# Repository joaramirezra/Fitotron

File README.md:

# Recamara de ambiente Controlado para germinar semillas de cannabis(Fitotron) 
### version : 0.2
### Fecha : 01/08/2021

**Antecedentes:** En el marco de la discusión de la propuesta del proyecto de ley sobre  regulación del consumo de cannabis con usos recreativo en Colombia, se han desarrollado debates en variados ámbitos algunos versan alrededor del cultivo,iacto economico, social, cultural  entre otros, por lo anterior se desarrolla un sistema de germinacion de semillas de cannabis, para poder impactar de manera positiva las primeras fases de la planta y con ellos contribuir en fases posteriores de crecimiento y cosecha.

**Descripción:**

### Requerimientos

**Hardware:**

- [ESP 8266](https://www.espressif.com/sites/default/files/documentation/0a-esp8266ex_datasheet_en.pdf)
- [Driver Actuadores](http://www.ti.com/lit/ds/symlink/uln2003a.pdf)
- [Sensor Humedad](https://www.sparkfun.com/datasheets/Sensors/Temperature/DHT22.pdf)
- [Raspberry pi]()

**Software:**

- [kicad 5.1.2](https://kicad-pcb.org/download/)
- [inventor 2019](https://www.autodesk.com/education/free-software/inventor-professional)
- [Arduino 18.1](https://www.arduino.cc/en/main/software)

### Colaboradores:
- [Johan Ramirez](https://github.com/joaramirezra)
- [Julio Cárdenas](https://github.com/julio-cardenas)

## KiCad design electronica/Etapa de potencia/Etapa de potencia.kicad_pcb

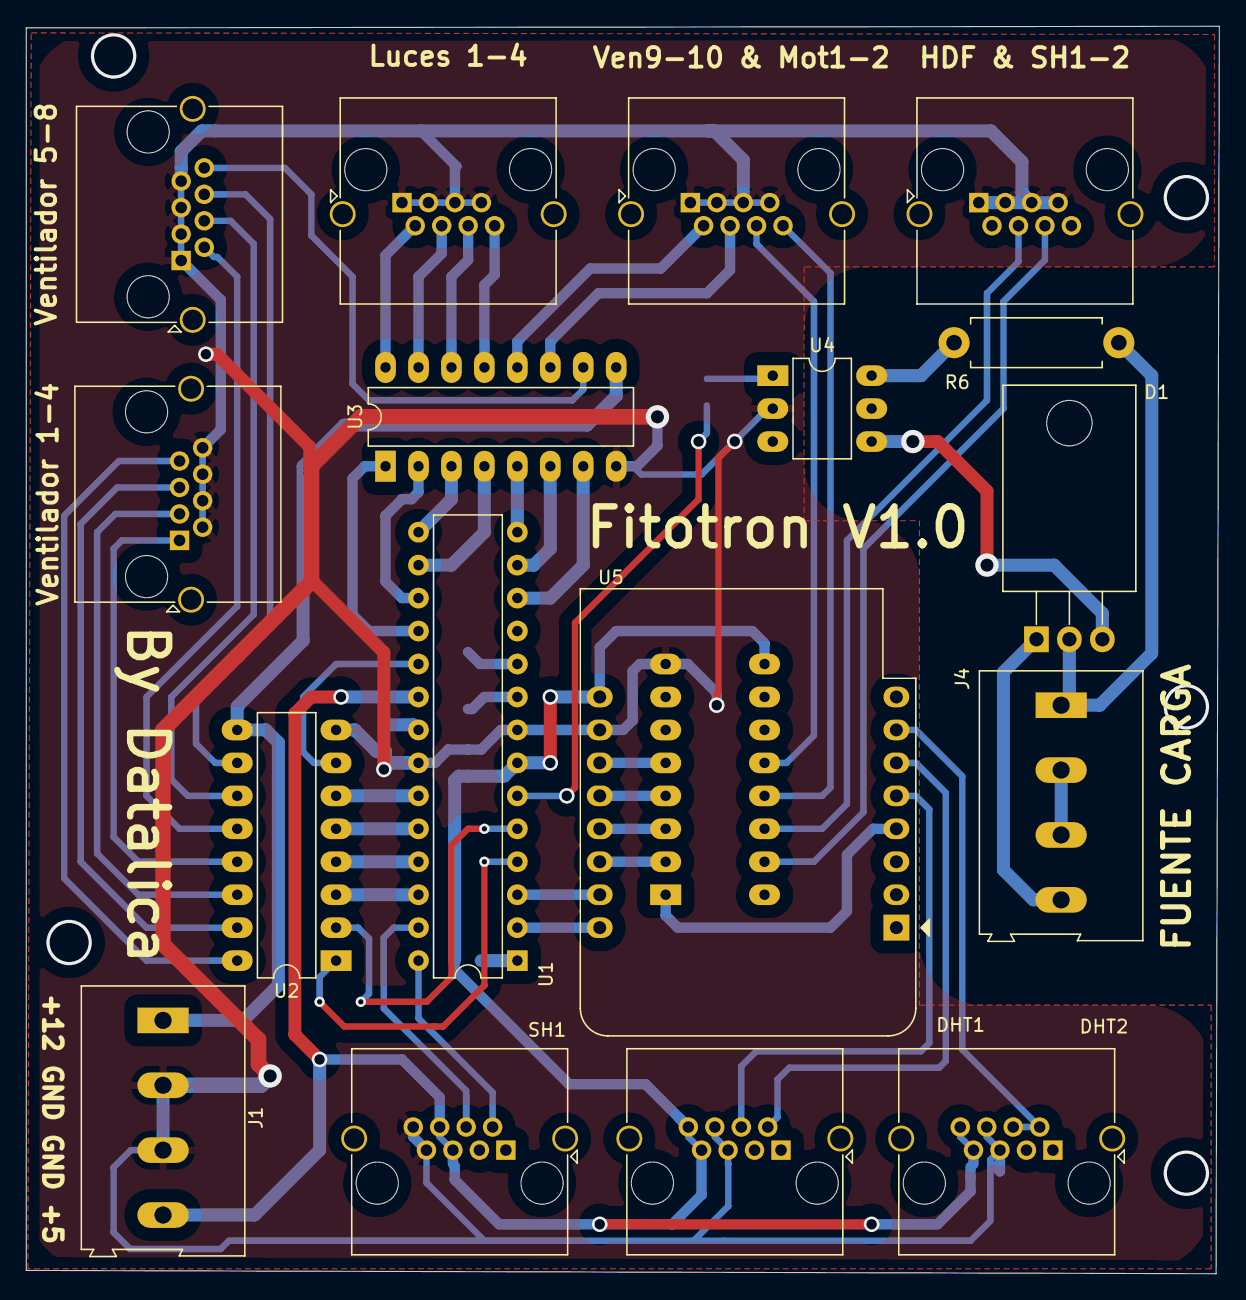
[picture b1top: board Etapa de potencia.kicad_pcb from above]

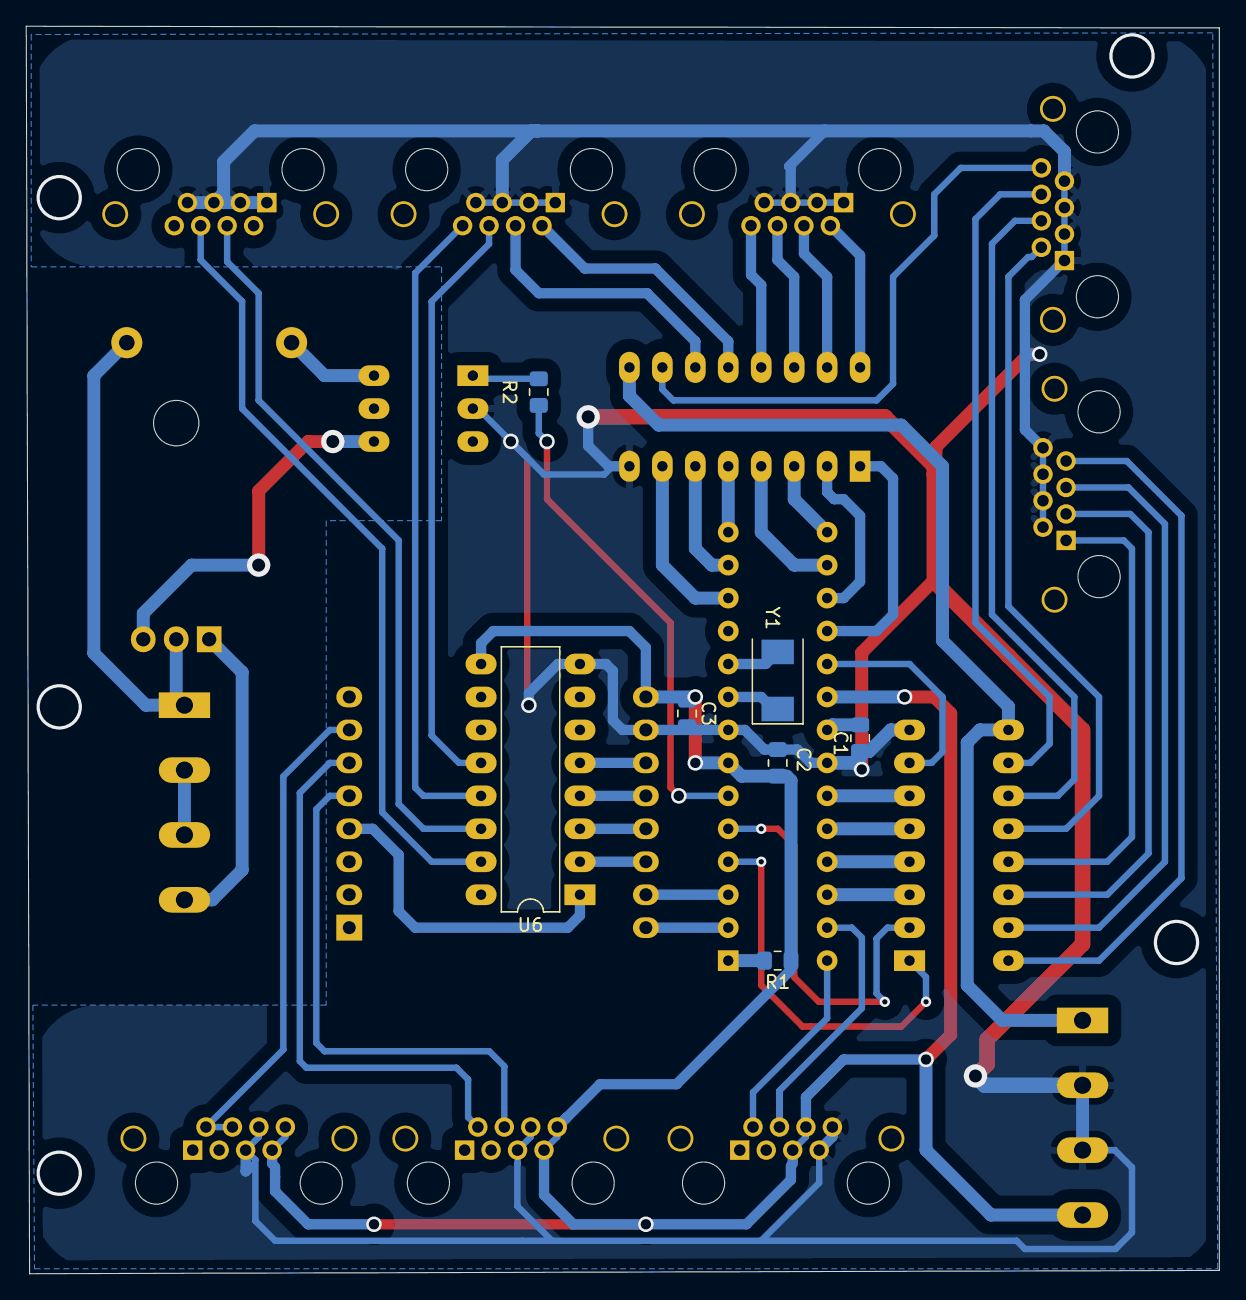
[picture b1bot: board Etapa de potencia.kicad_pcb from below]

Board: 2 copper layers, 91.9 x 96.1 mm, 24 parts (7 on the bottom side), 58 nets.

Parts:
C1: 100nF; C_0805_2012Metric_Pad1.15x1.40mm_HandSolder
C2, C3: 10uF; C_0805_2012Metric_Pad1.15x1.40mm_HandSolder
D1: BTA16; TO-220-3_Horizontal_TabDown
DHT1, DHT2: RJ45; RJ45_Amphenol_RJHSE5380
HDF & SH1-2: RJ45; RJ45_Amphenol_RJHSE5380
J1, J4: Bornera 4 pines; TerminalBlock_Altech_AK300-4_P5.00mm
Luces 1-4: RJ45; RJ45_Amphenol_RJHSE5380
R1: 10K; R_0805_2012Metric_Pad1.15x1.40mm_HandSolder
R2: 470; R_0805_2012Metric_Pad1.15x1.40mm_HandSolder
R6: 100; R_Axial_DIN0411_L9.9mm_D3.6mm_P12.70mm_Horizontal
SH1: RJ45; RJ45_Amphenol_RJHSE5380
U1: ATmega328-PU; DIP-28_W7.62mm
U2, U3: ULN2003; DIP-16_W7.62mm_LongPads
U4: MOC3031M; DIP-6_W7.62mm_LongPads
U5: WeMos_D1_mini; WEMOS_D1_mini_light
U6: ULN2002A; DIP-16_W7.62mm_LongPads
Ven9-10 & Mot1-2: RJ45; RJ45_Amphenol_RJHSE5380
Ventilador 1-4, Ventilador 5-8: RJ45; RJ45_Amphenol_RJHSE5380
Y1: Crystal; Crystal_SMD_0603-2Pin_6.0x3.5mm

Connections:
+5V: C2.1, C3.1, DHT1.7, DHT1.8, DHT2.7, DHT2.8, J1.4, R1.1, SH1.5, SH1.6, U1.7, U1.20, U5.9, U6.9
+12V: J1.1, U2.9, U3.9
Calentador: R2.2, U1.6
DHT_I1: DHT1.4, U5.5
DHT_I2: DHT1.2, U5.6
DHT_I3: DHT2.2, DHT2.4, U5.7
GND: C1.2, C2.2, C3.2, DHT1.5, DHT1.6, DHT2.5, DHT2.6, HDF & SH1-2.1, HDF & SH1-2.3, HDF & SH1-2.5, HDF & SH1-2.7, J1.2, J1.3, Luces 1-4.1, Luces 1-4.3, Luces 1-4.5, Luces 1-4.7, SH1.7, SH1.8, U1.8, U1.22, U2.8, U3.8, U4.2, U5.10, U6.8, Ven9-10 & Mot1-2.1, Ven9-10 & Mot1-2.3, Ven9-10 & Mot1-2.5, Ven9-10 & Mot1-2.7, Ventilador 1-4.2, Ventilador 1-4.4, Ventilador 1-4.6, Ventilador 1-4.8, Ventilador 5-8.1, Ventilador 5-8.3, Ventilador 5-8.5, Ventilador 5-8.7
H1: U5.4, U6.1
L1: U1.15, U3.3
L2: U1.14, U3.5
L3: U1.13, U3.6
L4: U1.12, U3.7
LO1: Luces 1-4.8, U3.13
LO2: Luces 1-4.6, U3.14
LO3: Luces 1-4.4, U3.15
LO4: Luces 1-4.2, U3.16
M1: U5.14, U6.2
M2: U5.13, U6.3
MO1: U6.13, Ven9-10 & Mot1-2.8
MO2: U6.12, Ven9-10 & Mot1-2.6
unnamed: C1.1, U1.21
unnamed: D1.1, J4.4
unnamed: D1.2, J4.1, R6.1
unnamed: D1.3, U4.4
unnamed: J4.2, J4.3
unnamed: R1.2, U1.1
unnamed: R2.1, U4.1
unnamed: R6.2, U4.6
unnamed: U1.9, Y1.1
unnamed: U1.10, Y1.2
PSH1: U5.12, U6.4
PSH2: U5.11, U6.5
PSHO1: HDF & SH1-2.6, U6.15
PSHO2: HDF & SH1-2.4, U6.14
RX: U1.2, U5.16
SH_I1: SH1.4, U1.27
SH_I2: SH1.2, U1.28
TX: U1.3, U5.15
V1: U1.5, U2.2
V2: U1.4, U2.1
V3: U1.26, U2.3
V4: U1.25, U2.4
V5: U1.24, U2.5
V6: U1.23, U2.6
V7: U1.19, U2.7
V8: U1.18, U3.1
V9: U1.17, U3.2
V10: U1.16, U3.4
VO1: U2.13, Ventilador 1-4.1
VO2: U2.14, Ventilador 1-4.3
VO3: U2.15, Ventilador 1-4.5
VO4: U2.16, Ventilador 1-4.7
VO5: U2.12, Ventilador 5-8.2
VO6: U2.11, Ventilador 5-8.4
VO7: U2.10, Ventilador 5-8.6
VO8: U3.10, Ventilador 5-8.8
VO9: U3.11, Ven9-10 & Mot1-2.4
VO10: U3.12, Ven9-10 & Mot1-2.2

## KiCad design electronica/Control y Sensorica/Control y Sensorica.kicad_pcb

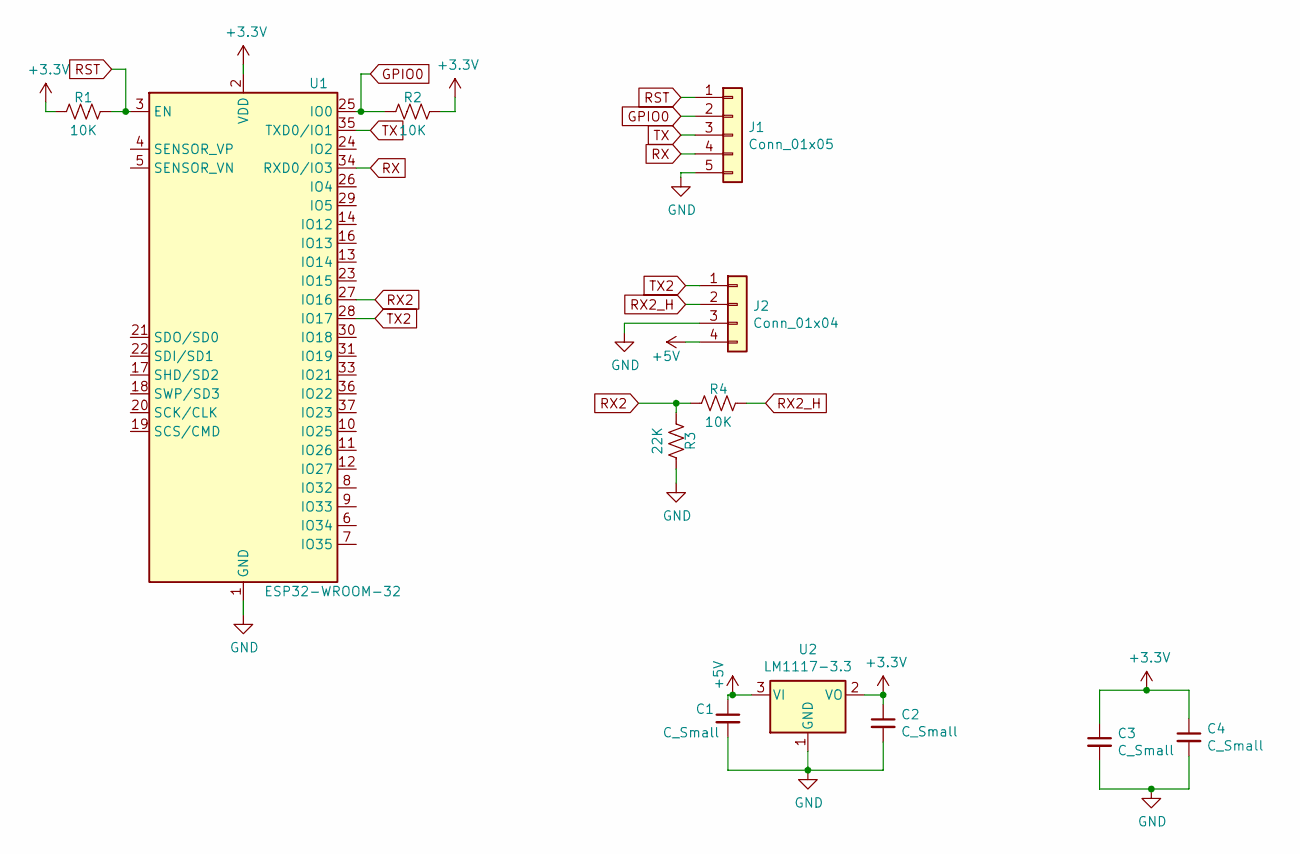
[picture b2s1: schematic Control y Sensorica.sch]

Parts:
C1, C2, C3, C4: C_Small; C_0805_2012Metric_Pad1.15x1.40mm_HandSolder
J1: Conn_01x05; PinHeader_1x05_P2.54mm_Horizontal
J2: Conn_01x04; PinSocket_1x04_P2.54mm_Vertical
R1, R2, R4: 10K; R_0805_2012Metric_Pad1.15x1.40mm_HandSolder
R3: 22K; R_0805_2012Metric_Pad1.15x1.40mm_HandSolder
U1: ESP32-WROOM-32
U2: LM1117-3.3; TO-252-2

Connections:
+3V3: C2.1, C3.1, C4.1, R1.2, R2.1, U1.2 (VDD), U2.2 (VO)
+5V: C1.1, J2.4, U2.3 (VI)
GND: C1.2, C2.2, C3.2, C4.2, J1.5, J2.3, R3.1, U1.1 (GND), U1.15 (GND), U1.38 (GND), U1.39 (GND), U2.1 (GND)
GPIO0: J1.2, R2.2, U1.25 (IO0)
RST: J1.1, R1.1, U1.3 (EN)
RX: J1.4, U1.34 (RXD0/IO3)
RX2: R3.2, R4.2, U1.27 (IO16)
RX2_H: J2.2, R4.1
TX: J1.3, U1.35 (TXD0/IO1)
TX2: J2.1, U1.28 (IO17)

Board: 2 copper layers, 12 parts (0 on the bottom side), 10 nets, no tracks yet.

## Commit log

2020-02-01 version 0
2020-02-01 version 0.1
2020-02-03 Electronica 0.5
2020-02-06 version 0.1 electronica
2020-02-06 Adding power stage
2020-02-08 Power Stage PCB ready to revision
2020-02-08 Adding a Control Stage baseline
2020-02-15 dashboard baselaine
2020-02-21 Programacion de la comunicacion entre el esp y el arduino, ademas se incluye la medicion de varaibles con el ESP
2020-02-21 funcina los tres sensores DHT22
2020-02-23 basic dashboard with firebase
2020-02-26 Version 0.8 firmware
2020-02-26 adding dynamic chart baseline
2020-02-28 adding contro-manual page
2020-03-02 ending first pcb
2020-03-03 ending control-panel | actuators
2020-03-24 Auto git commit
2021-07-09 inicial commit germinador
2021-07-09 commit with controller
2021-07-10 simple control interface
2021-07-13 something new mqtt init
2021-07-14 working on the firmware of the node actuadors
2021-08-18 v0 fitotron
2021-08-19 adding the triggers on firmware actuadors
2021-08-20 commit prueba
2022-02-11 Bump karma from 4.1.0 to 6.3.14 in /cloudProgramming/dashboard
    Bumps [karma](https://github.com/karma-runner/karma) from 4.1.0 to 6.3.14.
    - [Release notes](https://github.com/karma-runner/karma/releases)
    - [Changelog](https://github.com/karma-runner/karma/blob/master/CHANGELOG.md)
    - [Commits](https://github.com/karma-runner/karma/compare/v4.1.0...v6.3.14)
    ---
    updated-dependencies:
2022-03-02 Bump karma from 4.1.0 to 6.3.16 in /cloudProgramming/dashboard
    Bumps [karma](https://github.com/karma-runner/karma) from 4.1.0 to 6.3.16.
    - [Release notes](https://github.com/karma-runner/karma/releases)
    - [Changelog](https://github.com/karma-runner/karma/blob/master/CHANGELOG.md)
    - [Commits](https://github.com/karma-runner/karma/compare/v4.1.0...v6.3.16)
    ---
    updated-dependencies:
2022-06-03 Bump @angular/core from 8.2.14 to 11.0.5 in /cloudProgramming/dashboard
    Bumps [@angular/core](https://github.com/angular/angular/tree/HEAD/packages/core) from 8.2.14 to 11.0.5.
    - [Release notes](https://github.com/angular/angular/releases)
    - [Changelog](https://github.com/angular/angular/blob/main/CHANGELOG.md)
    - [Commits](https://github.com/angular/angular/commits/11.0.5/packages/core)
    ---
    updated-dependencies:
2023-05-07 Bump jszip from 3.2.2 to 3.10.1 in /cloudProgramming/dashboard
    Bumps [jszip](https://github.com/Stuk/jszip) from 3.2.2 to 3.10.1.
    - [Changelog](https://github.com/Stuk/jszip/blob/main/CHANGES.md)
    - [Commits](https://github.com/Stuk/jszip/compare/v3.2.2...v3.10.1)
    ---
    updated-dependencies:
    - dependency-name: jszip
2023-05-07 Bump qs from 6.4.0 to 6.4.1 in /cloudProgramming/dashboard
    Bumps [qs](https://github.com/ljharb/qs) from 6.4.0 to 6.4.1.
    - [Changelog](https://github.com/ljharb/qs/blob/main/CHANGELOG.md)
    - [Commits](https://github.com/ljharb/qs/compare/v6.4.0...v6.4.1)
    ---
    updated-dependencies:
    - dependency-name: qs
2023-05-07 Bump jsonwebtoken and firebase-tools in /cloudProgramming/dashboard
    Removes [jsonwebtoken](https://github.com/auth0/node-jsonwebtoken). It's no longer used after updating ancestor dependency [firebase-tools](https://github.com/firebase/firebase-tools). These dependen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
    Removes `jsonwebtoken`
    Updates `firebase-tools` from 7.13.1 to 11.30.0
    - [Release notes](https://github.com/firebase/firebase-tools/releases)
    - [Commits](https://github.com/firebase/firebase-tools/compare/v7.13.1...v11.30.0)
    ---
2023-05-07 Bump minimist, mkdirp, karma and protractor
    Bumps [minimist](https://github.com/minimistjs/minimist) to 1.2.8 and updates ancestor dependencies [minimist](https://github.com/minimistjs/minimist), [mkdirp](https://github.com/isaacs/node-mkdirp)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
    Updates `minimist` from 1.2.0 to 1.2.8
    - [Changelog](https://github.com/minimistjs/minimist/blob/main/CHANGELOG.md)
    - [Commits](https://github.com/minimistjs/minimist/compare/v1.2.0...v1.2.8)
    Updates `mkdirp` from 0.5.1 to 0.5.6
    - [Changelog](https://github.com/isaacs/node-mkdirp/blob/main/CHANGELOG
